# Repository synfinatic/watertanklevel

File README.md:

# Water Tank Level and Relay Control

ESP8266 ultrasonic water tank level module.

Reports water tank levels and controls a relay to cut off a pump before the
tank goes dry.

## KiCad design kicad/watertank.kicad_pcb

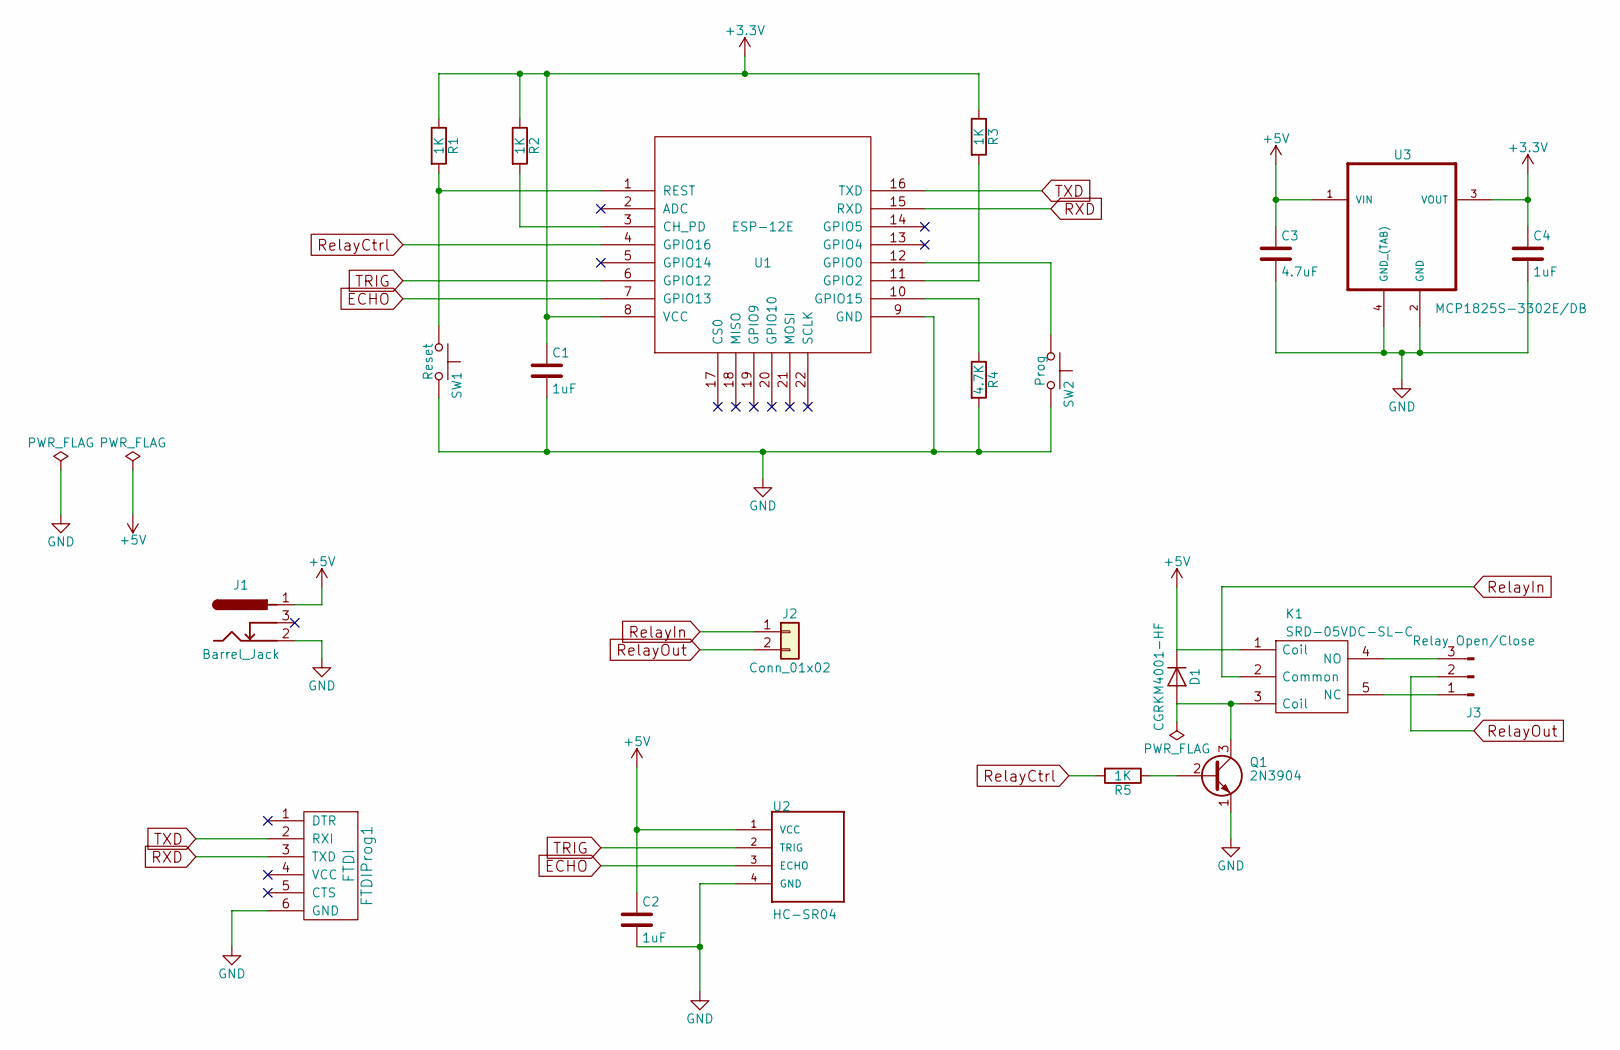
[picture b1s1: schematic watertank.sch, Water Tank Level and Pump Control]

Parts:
C1, C2, C4: 1uF; C_0805_HandSoldering
C3: 4.7uF; C_0805_HandSoldering
D1: CGRKM4001-HF; D_SOD-123F
FTDIProg1: FTDI; FTDIHeader
J1: Barrel_Jack; BARREL_JACK
J2: Conn_01x02; PhoenixContact_MSTBA-G_02x5.08mm_Angled
J3: Relay Open/Close; Pin_Header_Straight_1x03_Pitch2.54mm
K1: SRD-05VDC-SL-C; Songle-SRD-05VDC-SL-C; Manufacturer_Part_Number SRD-05VDC-SL-C
Q1: 2N3904; SOT-23_Handsoldering
R1, R2, R3, R5: 1K; R_0805_HandSoldering
R4: 4.7K; R_0805_HandSoldering
SW1: Reset; SPST-SMD-6x3.5
SW2: Prog; SPST-SMD-6x3.5
U1: ESP-12E; ESP-12E_SMD
U2: HC-SR04; HC-SR04-Horizontal
U3: MCP1825S-3302E/DB; SOT-223

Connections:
+3V3: C1.1, C4.1, R1.1, R2.1, R3.1, U1.8 (VCC), U3.3 (VOUT)
+5V: C2.1, C3.1, D1.1 (K), J1.1, K1.1 (Coil), U2.1 (VCC), U3.1 (VIN)
ECHO: U1.7 (GPIO13), U2.3 (ECHO)
GND: C1.2, C2.2, C3.2, C4.2, FTDIProg1.6 (GND), J1.2, Q1.1 (E), R4.2, SW1.2, SW2.2, U1.9 (GND), U2.4 (GND), U3.2 (GND), U3.4 (GND_(TAB))
unnamed: D1.2 (A), K1.3 (Coil), Q1.3 (C)
unnamed: J3.1, K1.5 (NC)
unnamed: J3.3, K1.4 (NO)
unnamed: Q1.2 (B), R5.1
unnamed: R1.2, SW1.1, U1.1 (REST)
unnamed: R2.2, U1.3 (CH_PD)
unnamed: R3.2, U1.11 (GPIO2)
unnamed: R4.1, U1.10 (GPIO15)
unnamed: SW2.1, U1.12 (GPIO0)
RXD: FTDIProg1.3 (TXD), U1.15 (RXD)
RelayCtrl: R5.2, U1.4 (GPIO16)
RelayIn: J2.1, K1.2 (Common)
RelayOut: J2.2, J3.2
TRIG: U1.6 (GPIO12), U2.2 (TRIG)
TXD: FTDIProg1.2 (RXI), U1.16 (TXD)

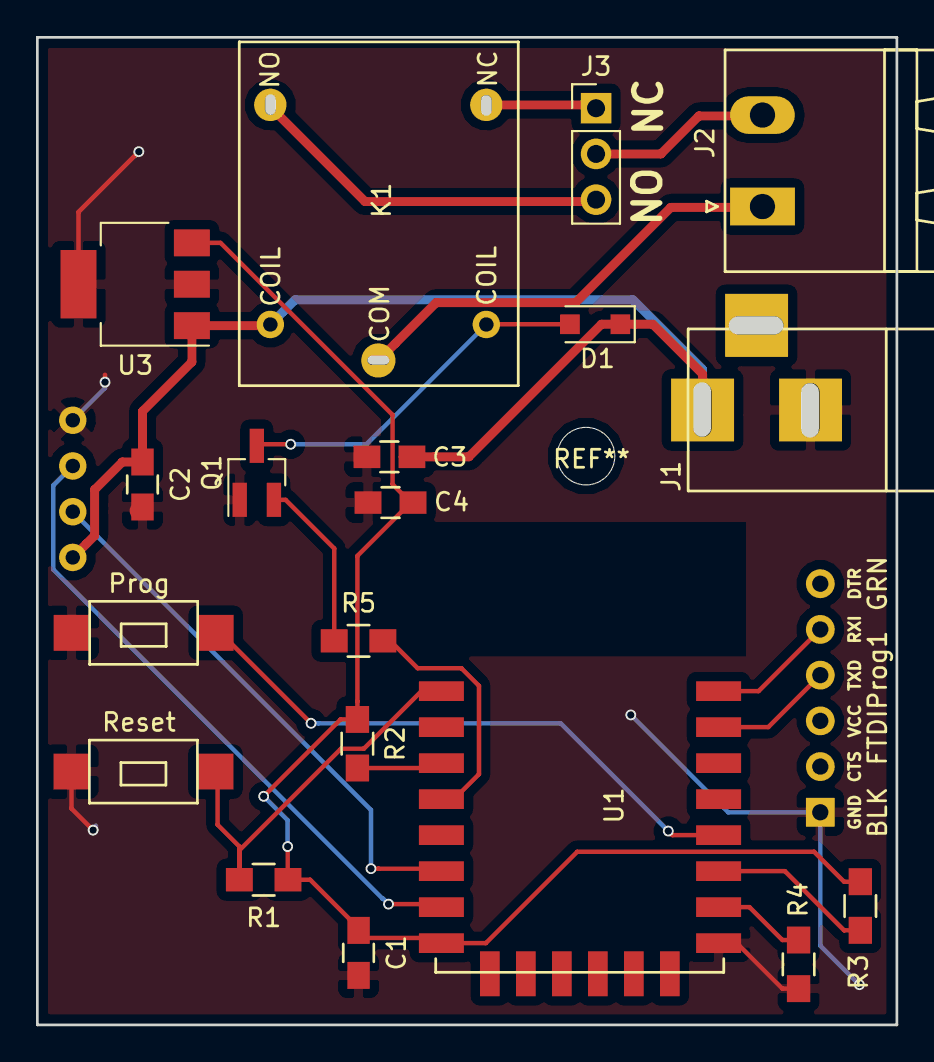
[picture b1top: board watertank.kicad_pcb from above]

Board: 2 copper layers, 46.9 x 54.0 mm, 21 parts (1 on the bottom side), 19 nets.

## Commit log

2018-03-04 add basic readme
2018-03-24 v1.0 of the board
    First generation board with ultra sonic distance
    and relay.
